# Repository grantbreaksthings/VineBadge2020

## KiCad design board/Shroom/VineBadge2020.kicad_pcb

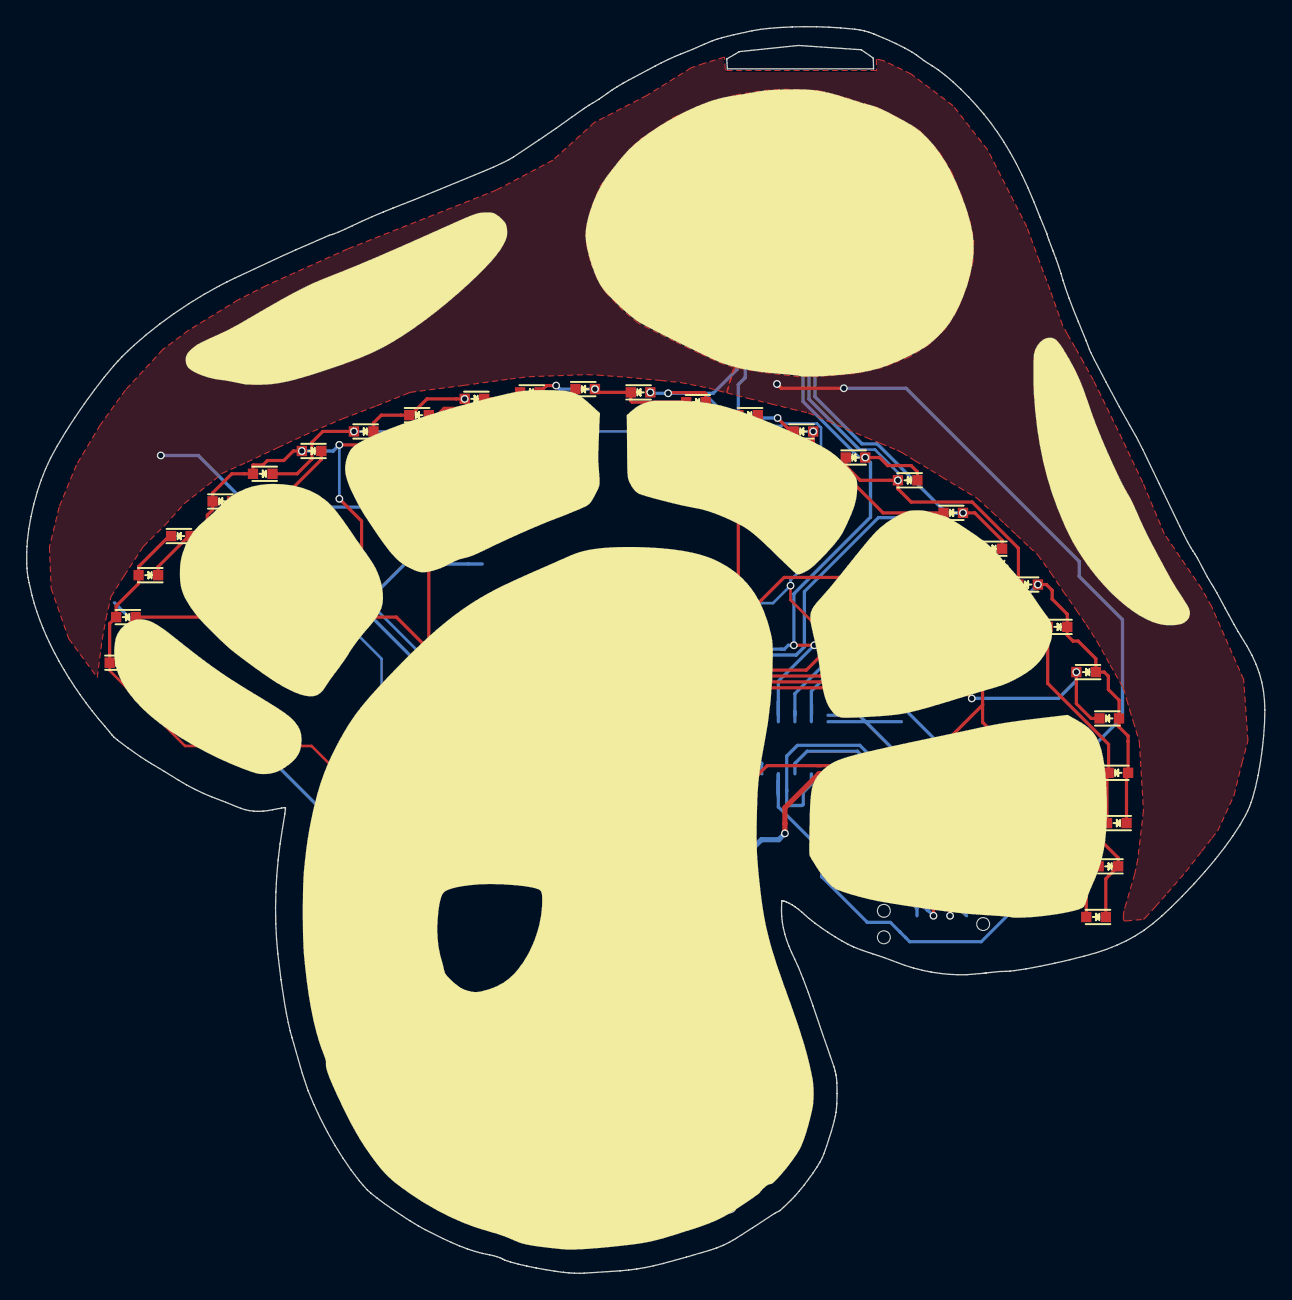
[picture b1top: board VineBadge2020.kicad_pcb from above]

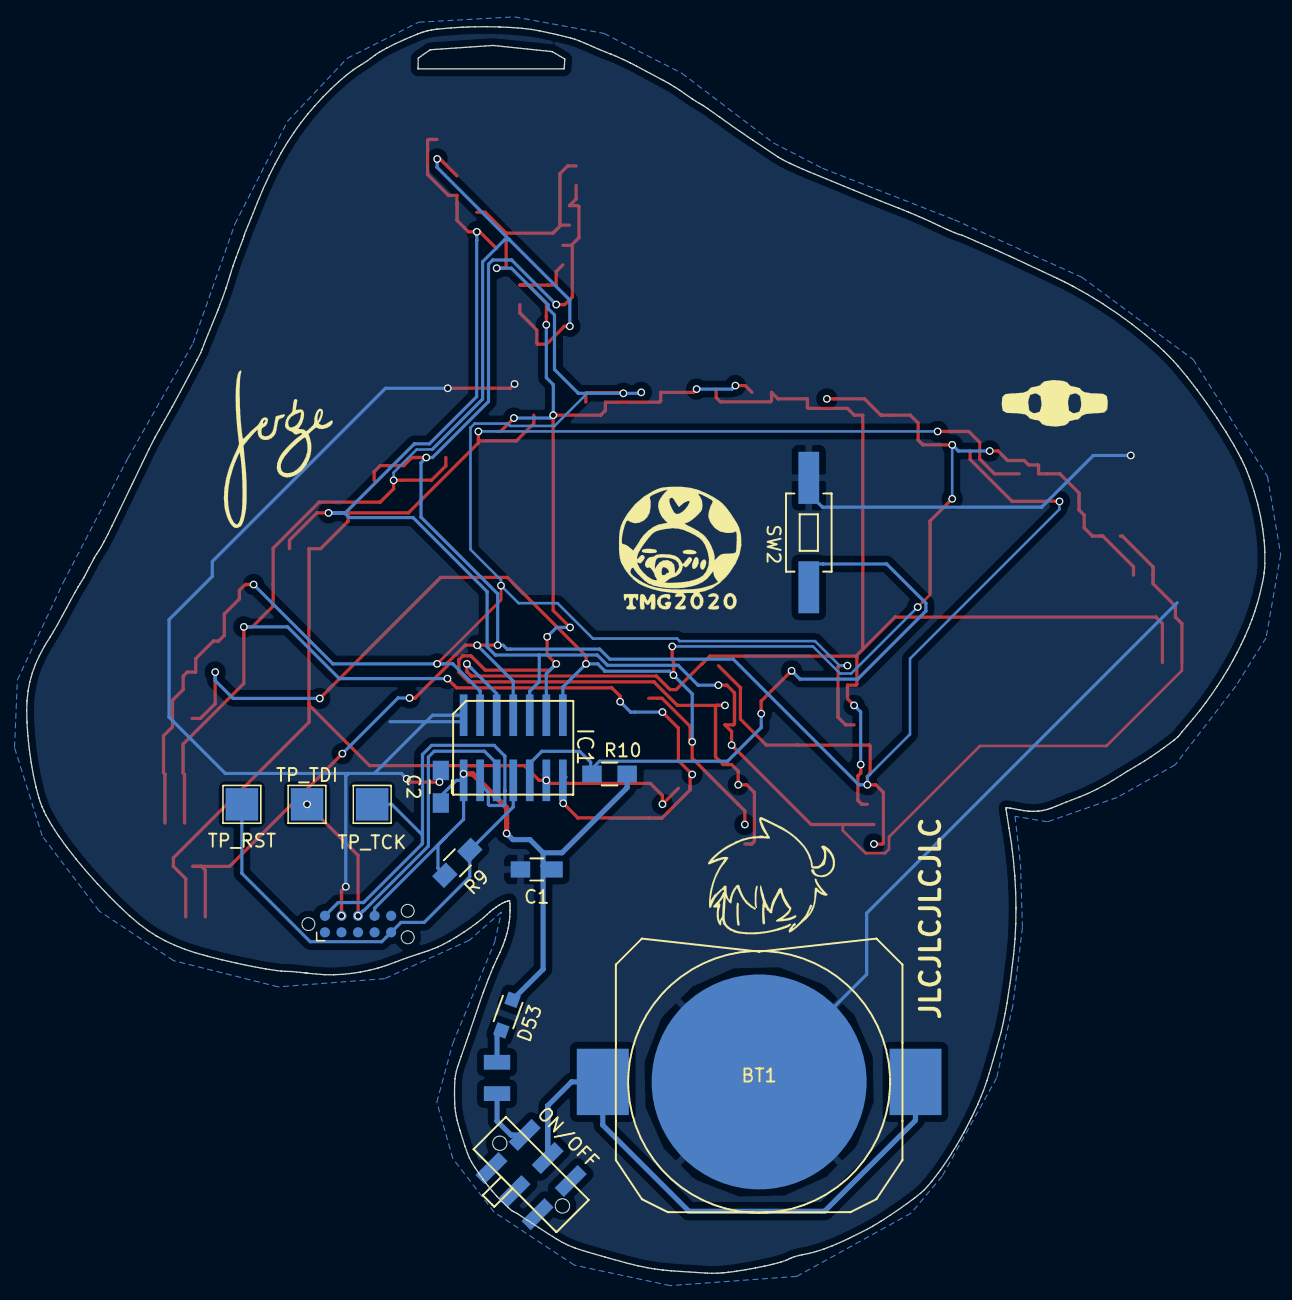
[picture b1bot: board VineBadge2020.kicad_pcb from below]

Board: 2 copper layers, 95.0 x 95.7 mm, 66 parts (14 on the bottom side), 17 nets.

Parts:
BT1: Battery_Cell; COINCELL_20MM_HANDSOLDER
C1: 100nF; C_0805_HandSoldering
C2: 1uF; C_0805_HandSoldering
D1, D2, D3, D4, D5, D6, D7, D8, D9, D10, D11, D12, D13, D14, D15, D16, D17, D18, D19, D20, D21, D22, D23, D24, D25, D26, D27, D28, D29, D30, D31, D32, D33, D34, D35, D36, D37, D38, D39, D40, D41, D42, D43, D44, D45, D46, D47, D48, D49, D50, D51, D52: LED; LED_0603
D53: D_Schottky; SOD-323_HandSoldering
F1: Fuse; Fuse_SMD1206_Reflow
IC1: ATTINY20-X; ATTINY20_SOIC-14-HANDSOLDER
J1: CONN-TAGCONNECT-TC2050; TC2050-All_Holes
ON/OFF: SW_SPDT; JS202011JAQN-Handsolder
R9, R10: 1K; R_0805_HandSoldering
SW2: SW_Push; SW_SPST_EVQPE1_Handsolder
TEST1: TP_TCK; TestPoint_Pad_2.5x2.5mm
TEST2: TP_TDI; TestPoint_Pad_2.5x2.5mm
TEST3: TP_RST; TestPoint_Pad_2.5x2.5mm

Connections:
+BATT: C1.1, C2.1, D53.1, IC1.1, J1.7, R9.2, R10.2
/BTN: IC1.5, R10.1, SW2.1
/RST: IC1.4, J1.5, R9.1, TEST3.1
/TCK: IC1.2, J1.10, TEST1.1
/TDI: IC1.3, J1.8, TEST2.1
GND: BT1.2, C1.2, C2.2, IC1.14, J1.9, SW2.2
unnamed: BT1.1, ON/OFF.2
unnamed: D1.1, D2.2, D8.2, D9.1, D17.2, D18.1, D25.2, D27.1, D39.2, D40.1, IC1.12
unnamed: D1.2, D8.1, D15.2, D16.1, D21.2, D23.1, D35.2, D37.1, D45.2, D46.1, D47.2, D48.1, D51.2, D52.1, IC1.13
unnamed: D2.1, D3.2, D9.2, D10.1, D15.1, D16.2, D19.2, D20.1, D29.2, D31.1, D41.2, D42.1, D49.2, D50.2, IC1.11
unnamed: D3.1, D4.2, D10.2, D11.1, D17.1, D18.2, D21.1, D22.2, D23.2, D24.1, D33.2, D34.1, D43.2, D44.1, IC1.10
unnamed: D4.1, D5.2, D11.2, D12.1, D19.1, D20.2, D25.1, D26.2, D27.2, D28.1, D35.1, D36.2, D37.2, D38.1, IC1.9
unnamed: D5.1, D6.2, D12.2, D13.1, D22.1, D24.2, D29.1, D30.2, D31.2, D32.1, D39.1, D40.2, D45.1, D46.2, IC1.8
unnamed: D6.1, D7.2, D13.2, D14.1, D26.1, D28.2, D33.1, D34.2, D41.1, D42.2, D47.1, D48.2, D51.1, D52.2, IC1.7
unnamed: D7.1, D14.2, D30.1, D32.2, D36.1, D38.2, D43.1, D44.2, D49.1, D50.1, IC1.6
unnamed: D53.2, F1.1
unnamed: F1.2, ON/OFF.1
